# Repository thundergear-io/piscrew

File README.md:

# Pi Screw
Pi Screw is a shield designed for Raspberry Pi Boards. The purpose of this shield is to make connecting a wide range of wires easier with the help of screw terminals and QWIIC connectors. 

Please refer to our documentation for more information and board compatibility:

https://github.com/thundergear-io/piscrew/blob/main/documentation/piscrew-documentation.pdf

# Front 

# Back

# Certification

# Contact

Need to contact us ? Send us an email at contact@thundergear.io

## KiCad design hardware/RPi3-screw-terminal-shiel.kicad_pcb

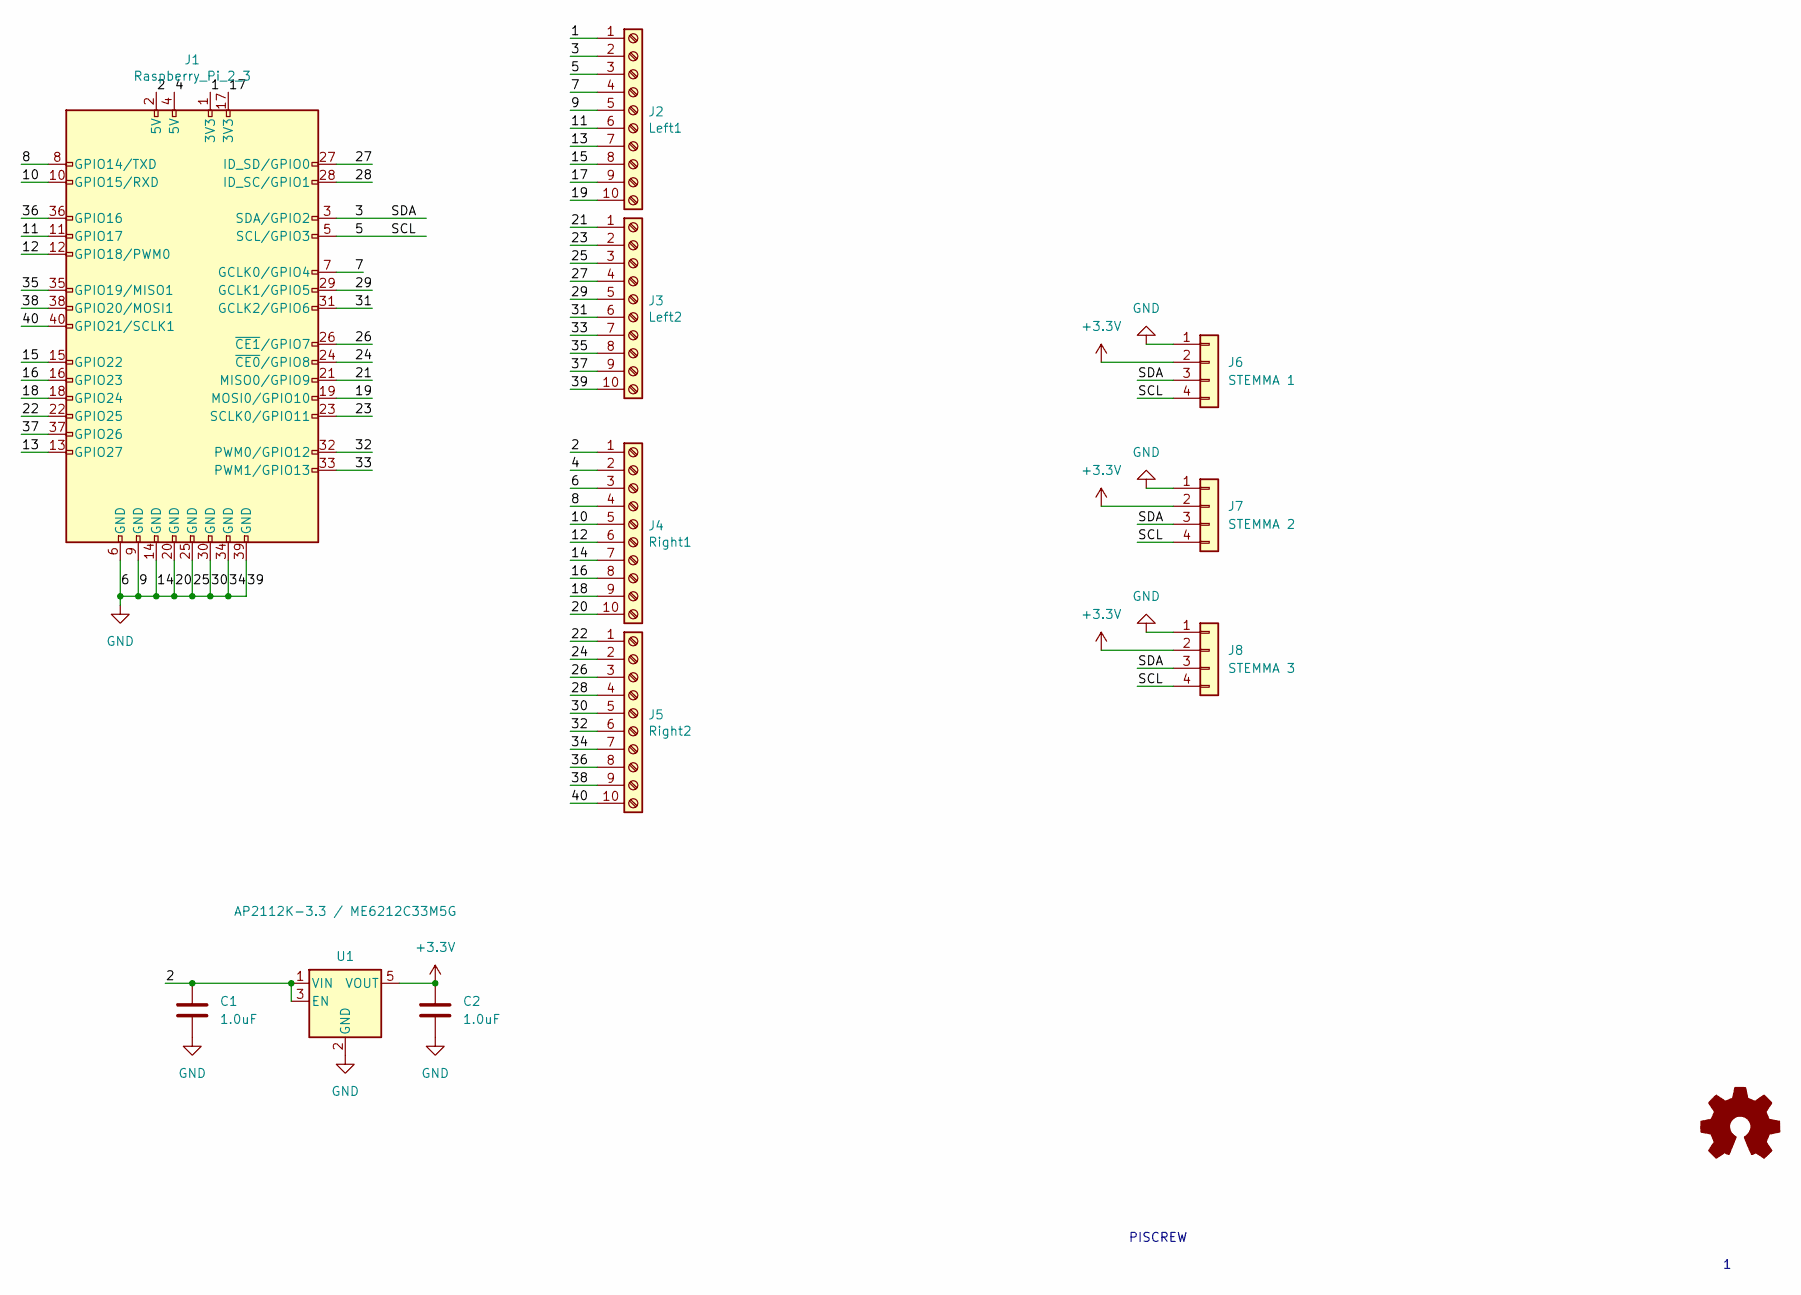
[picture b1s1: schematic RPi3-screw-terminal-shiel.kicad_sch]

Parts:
C1, C2: 1.0uF
J1: Raspberry_Pi_2_3
J2: Left1
J3: Left2
J4: Right1
J5: Right2
J6: STEMMA 1
J7: STEMMA 2
J8: STEMMA 3
U1: AP2112K-3.3 / ME6212C33M5G; SOT-23-5

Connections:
+3V3: C2.1, J6.2, J7.2, J8.2, U1.5 (VOUT)
/1: J1.1 (3V3), J2.1
/2: C1.1, J1.2 (5V), J4.1, U1.1 (VIN), U1.3 (EN)
/3: J1.3 (SDA/GPIO2), J2.2, J6.3, J7.3, J8.3
/4: J1.4 (5V), J4.2
/5: J1.5 (SCL/GPIO3), J2.3, J6.4, J7.4, J8.4
/7: J1.7 (GCLK0/GPIO4), J2.4
/8: J1.8 (GPIO14/TXD), J4.4
/10: J1.10 (GPIO15/RXD), J4.5
/11: J1.11 (GPIO17), J2.6
/12: J1.12 (GPIO18/PWM0), J4.6
/13: J1.13 (GPIO27), J2.7
/15: J1.15 (GPIO22), J2.8
/16: J1.16 (GPIO23), J4.8
/17: J1.17 (3V3), J2.9
/18: J1.18 (GPIO24), J4.9
/19: J1.19 (MOSI0/GPIO10), J2.10
/21: J1.21 (MISO0/GPIO9), J3.1
/22: J1.22 (GPIO25), J5.1
/23: J1.23 (SCLK0/GPIO11), J3.2
/24: J1.24 (~CE0/GPIO8), J5.2
/26: J1.26 (~CE1/GPIO7), J5.3
/27: J1.27 (ID_SD/GPIO0), J3.4
/28: J1.28 (ID_SC/GPIO1), J5.4
/29: J1.29 (GCLK1/GPIO5), J3.5
/31: J1.31 (GCLK2/GPIO6), J3.6
/32: J1.32 (PWM0/GPIO12), J5.6
/33: J1.33 (PWM1/GPIO13), J3.7
/35: J1.35 (GPIO19/MISO1), J3.8
/36: J1.36 (GPIO16), J5.8
/37: J1.37 (GPIO26), J3.9
/38: J1.38 (GPIO20/MOSI1), J5.9
/40: J1.40 (GPIO21/SCLK1), J5.10
GND: C1.2, C2.2, J1.6 (GND), J1.9 (GND), J1.14 (GND), J1.20 (GND), J1.25 (GND), J1.30 (GND), J1.34 (GND), J1.39 (GND), J2.5, J3.3, J3.10, J4.3, J4.7, J4.10, J5.5, J5.7, J6.1, J7.1, J8.1, U1.2 (GND)

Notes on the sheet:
PISCREW

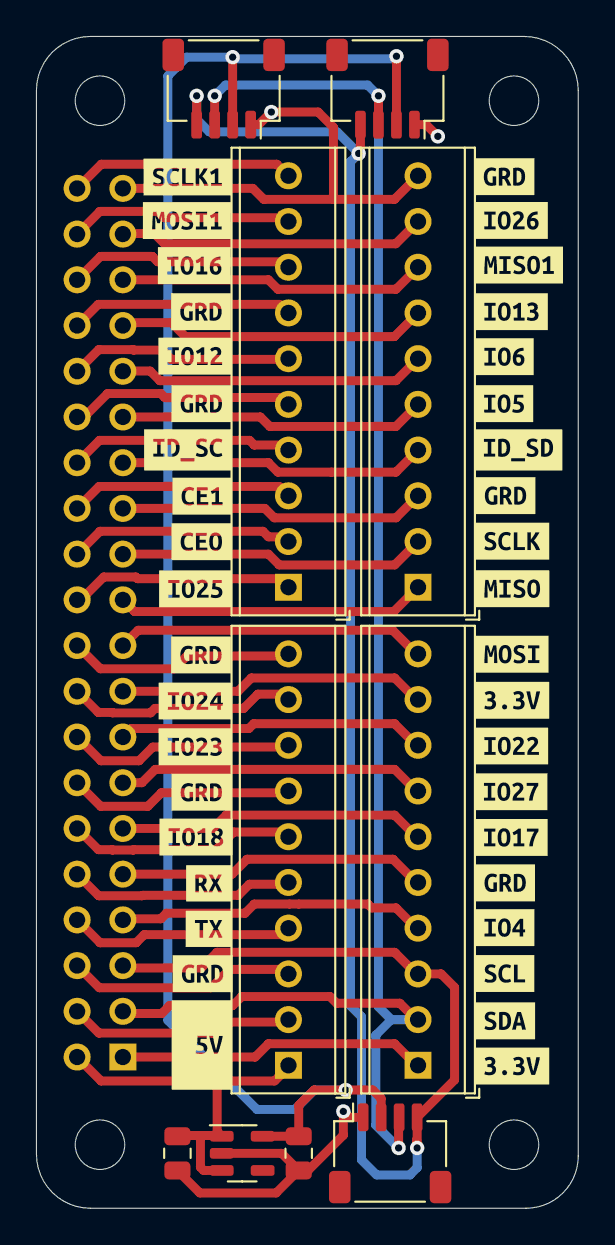
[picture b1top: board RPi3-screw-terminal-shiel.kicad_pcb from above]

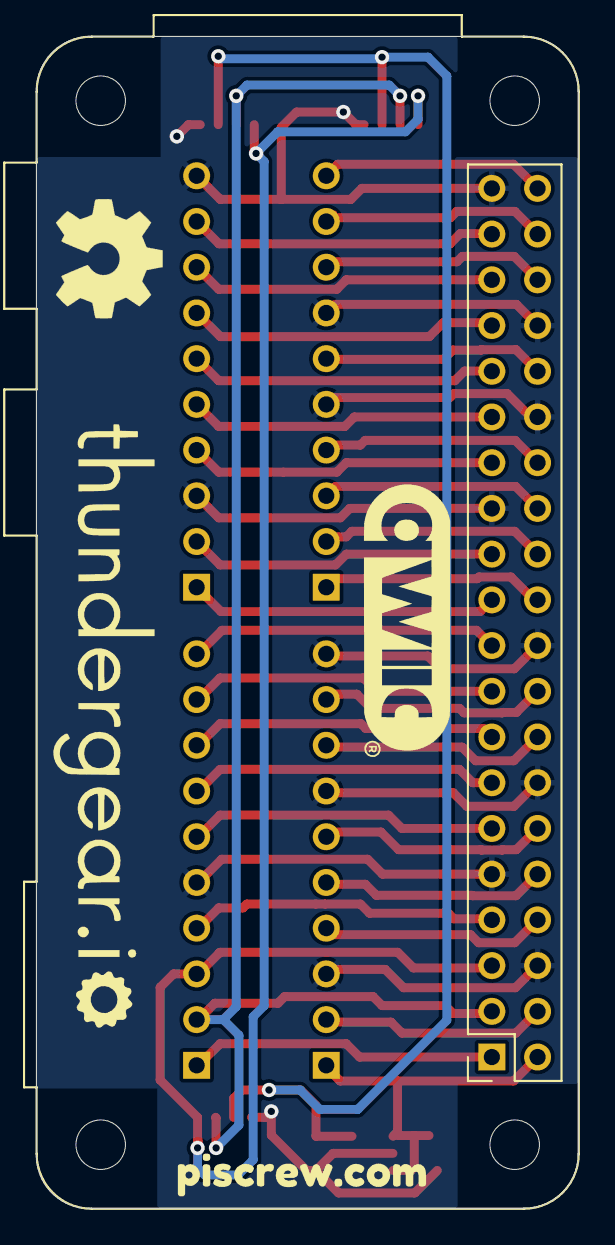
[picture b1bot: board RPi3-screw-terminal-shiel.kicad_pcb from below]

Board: 2 copper layers, 30.1 x 65.1 mm, 51 parts (2 on the bottom side), 34 nets.

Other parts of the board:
kibuzzard-61EAB5A7: G***; kibuzzard-61EAB5A7
kibuzzard-61EAB5AF: G***; kibuzzard-61EAB5AF
kibuzzard-61EAB5B7: G***; kibuzzard-61EAB5B7
kibuzzard-61EAB5BF: G***; kibuzzard-61EAB5BF
kibuzzard-61EAB5C9: G***; kibuzzard-61EAB5C9
kibuzzard-61EAB5E7: G***; kibuzzard-61EAB5E7
kibuzzard-61EAB7AC: G***; kibuzzard-61EAB7AC
kibuzzard-61EAB7BB: G***; kibuzzard-61EAB7BB
kibuzzard-61EAB7C8: G***; kibuzzard-61EAB7C8
kibuzzard-61EAB7D1: G***; kibuzzard-61EAB7D1
kibuzzard-61EAB7DA: G***; kibuzzard-61EAB7DA
kibuzzard-61EAB8A6: G***; kibuzzard-61EAB8A6
kibuzzard-61EAB8B0: G***; kibuzzard-61EAB8B0
kibuzzard-61EAB44C: G***; kibuzzard-61EAB44C
kibuzzard-61EAB46F: G***; kibuzzard-61EAB46F
kibuzzard-61EAB52D: G***; kibuzzard-61EAB52D
kibuzzard-61EAB57E: G***; kibuzzard-61EAB57E
kibuzzard-61EAB58D: G***; kibuzzard-61EAB58D
kibuzzard-61EAB59E: G***; kibuzzard-61EAB59E
kibuzzard-61EAB79F: G***; kibuzzard-61EAB79F
kibuzzard-61EAB88A: G***; kibuzzard-61EAB88A
kibuzzard-61EAB89C: G***; kibuzzard-61EAB89C
kibuzzard-61EAB517: G***; kibuzzard-61EAB517
kibuzzard-61EAB524: G***; kibuzzard-61EAB524
kibuzzard-61EAB538: G***; kibuzzard-61EAB538
kibuzzard-61EAB545: G***; kibuzzard-61EAB545
kibuzzard-61EAB559: G***; kibuzzard-61EAB559
kibuzzard-61EAB567: G***; kibuzzard-61EAB567
kibuzzard-61EAB573: G***; kibuzzard-61EAB573
kibuzzard-61EAB596: G***; kibuzzard-61EAB596
kibuzzard-61EAB753: G***; kibuzzard-61EAB753
kibuzzard-61EAB790: G***; kibuzzard-61EAB790
kibuzzard-61EAB798: G***; kibuzzard-61EAB798
kibuzzard-61EAB879: G***; kibuzzard-61EAB879
kibuzzard-61EAB880: G***; kibuzzard-61EAB880
kibuzzard-61EAB894: G***; kibuzzard-61EAB894
kibuzzard-61EAD2A5: G***; kibuzzard-61EAD2A5
kibuzzard-61EAD2B4: G***; kibuzzard-61EAD2B4
kibuzzard-61EAD2FB: G***; kibuzzard-61EAD2FB
kibuzzard-6217C81B: G***; kibuzzard-6217C81B

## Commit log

2022-04-15 Create LICENSE
